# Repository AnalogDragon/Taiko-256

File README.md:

# Taiko-256  
Taiko JVS for Namco System 256 (246)  

Previously, running Taiko on Namco System 256 required many accessories, such as a JVS (MINI-JV PCB), a SIF PCB, and an intermediate FUTA PCB, making the setup overly complex.  
This project's PCB can fully replace the three boards mentioned above. It features two independent Taiko interfaces, an onboard Service button, and supports direct power supply via ATX.  
Alternatively, this PCB can also be used to replace only the SIF PCB and FUTA PCB while still using the original MINI-JV PCB. However, this does not provide a better experience.  

## PCB:  

**Labels in the image:**  
- **A**: Taiko sensor interface. Channels 1\~4 are for Player 1, and channels 5\~8 are for Player 2. Requires connection to a Taiko with vibration sensors (the pins near the board edge are for grounding).  
- **B**: Taiko sensor input swap matrix. Jumpers can be placed in different positions to map inputs to any channel.  
- **C**: Interface for connecting to MINI-JV (can be left unconnected).  
- **D**: When connecting to MINI-JV, determines whether drum signals come from the MCU or SIF (can be left unconnected).  
- **E**: Requires three jumpers to be vertically shorted. If MINI-JV is connected, remove all three jumpers.  
- **F**: Interface for connecting to System 256. Either vertical or right-angle connectors can be soldered (ensure correct placement). For data communication, a USB-A to USB-B cable is required. For System 256 power, a VH3.96-6Pin double-ended reverse cable is needed.  
- **G**: ATX power connector. Either vertical or right-angle connectors can be soldered.  
- **H**: Power switch (requires a latching switch). Press to activate the ATX power supply.  
- **I**: Used for debug.  
- **J**: Configuration code (from left to right, digits 1~4):  
  - **1**: Debug switch (set to OFF during use).  
  - **2**: Frequency limiter switch (set to ON during use, as the System cannot handle overly fast inputs).  
  - **3**: Automatic DON allocation (if the left DON is hit multiple times, System 256 may fail to recognize excessive inputs. Allocating it to the right channel improves the experience. Recommended: ON).  
  - **4**: JVS function (set to ON. Set to OFF if connecting to MINI-JV).  
- **K**: Service function buttons. TEST requires a latching switch, while the others require momentary switches.  
- **L**: Connector for linking to a Service control panel. If the Service buttons need to be extended to another panel, this connector can be used.  

### PCB Image:

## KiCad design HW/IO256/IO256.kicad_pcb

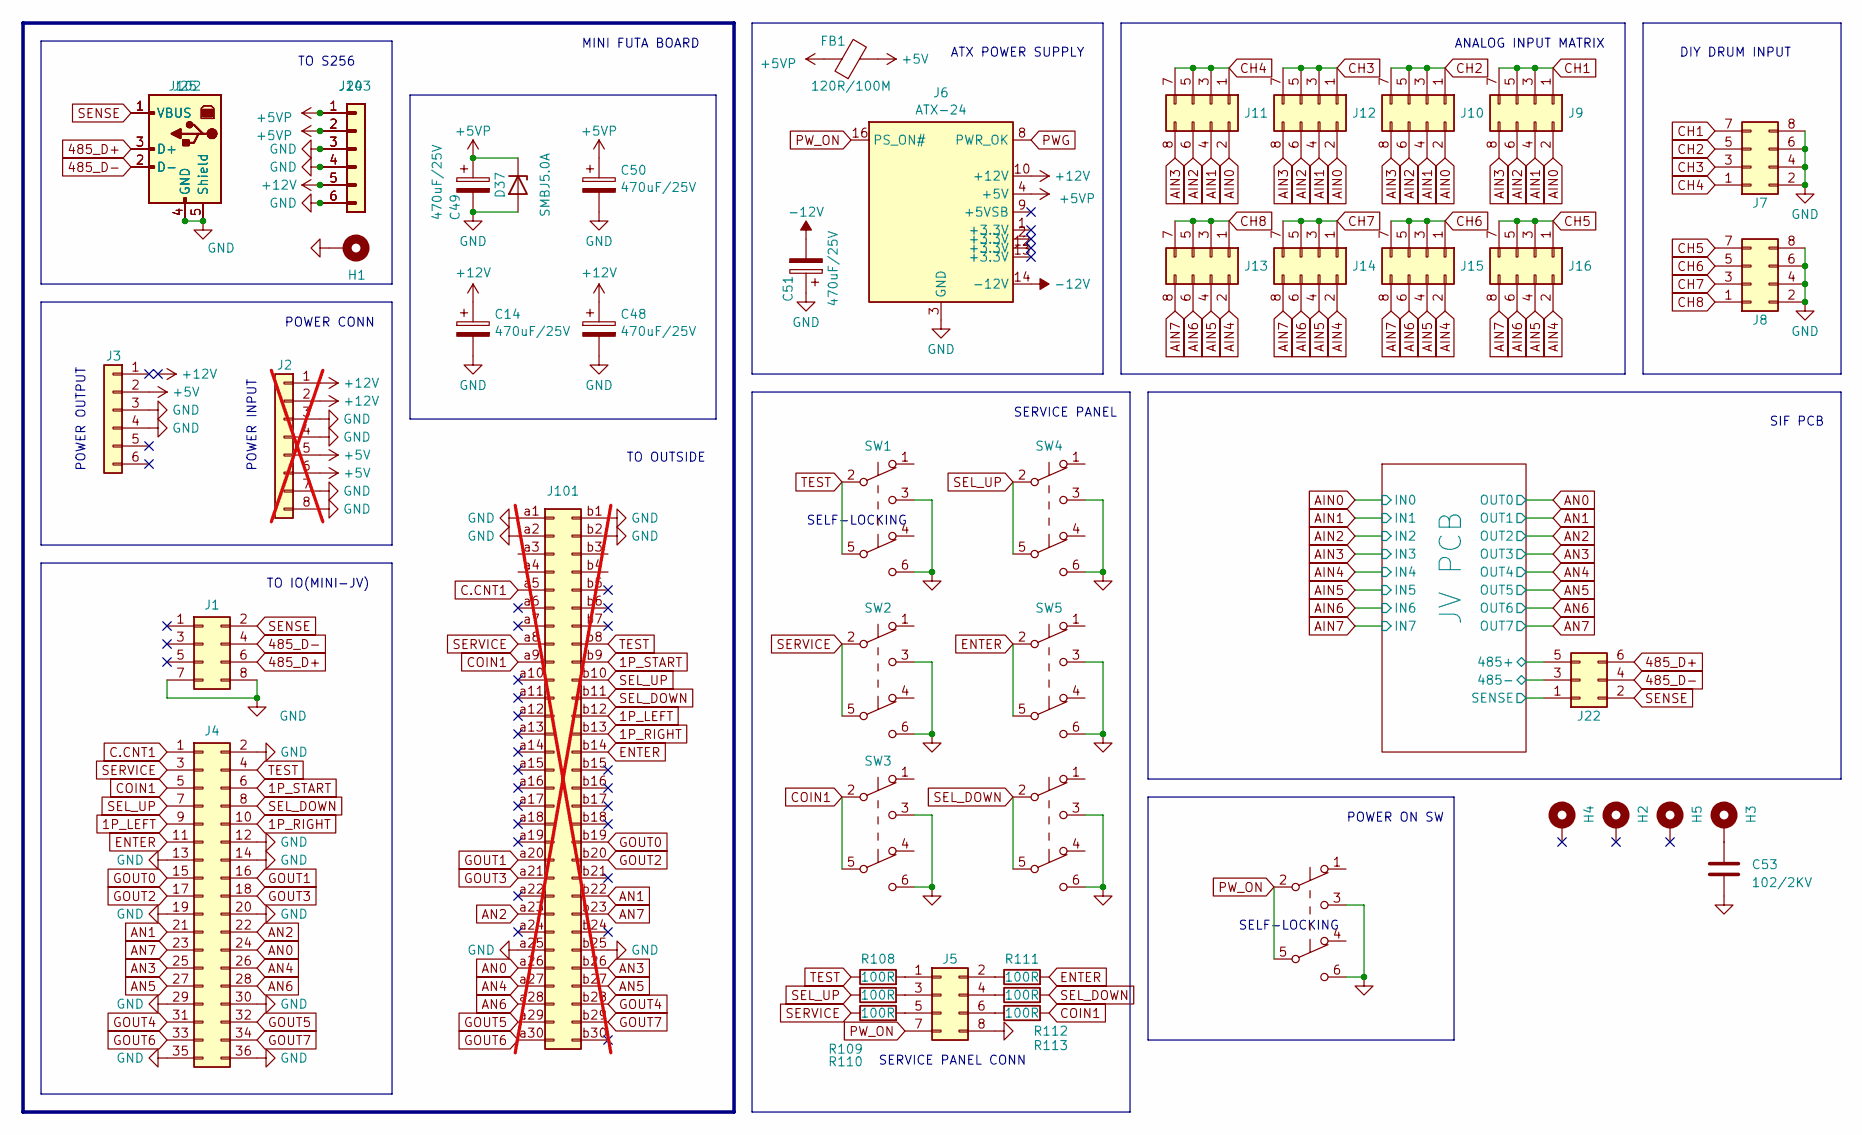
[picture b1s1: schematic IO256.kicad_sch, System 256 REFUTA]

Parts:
C14, C48, C49, C50, C51: 470uF/25V; CP_Radial_D8.0mm_P3.50mm
C53: 102/2KV; C_1206_3216Metric
D37: SMBJ5.0A; D_SMB
FB1: 120R/100M; R_0805_2012Metric
H1, H2, H3, H4, H5: MINI-JV; MountingHole_3.2mm_M3_DIN965_Pad
J1: Conn_02x04_Odd_Even; B08B-XADSS-N-A
J2: Conn_01x08; JST_VH_B8P-VH-B_1x08_P3.96mm_Vertical; not fitted
J3, J103: Conn_01x06; JST_VH_B6P-VH_1x06_P3.96mm_Vertical
J4: Conn_02x18_Odd_Even; B36B-XADSS-N-A
J5, J7, J8: Conn_02x04_Counter_Clockwise; IDC-Header_2x04_P2.54mm_Vertical
J6: ATX-24; 5557-2x12
J9, J10, J11, J12, J13, J14, J15, J16: Conn_02x04_Counter_Clockwise; PinHeader_2x04_P2.54mm_Vertical
J22: Conn_02x02_Odd_Even; PinHeader_2x03_P2.54mm_Vertical
J24: Conn_01x06; JST_VH_B6PS-VH_1x06_P3.96mm_Horizontal
J25: USB_B; USB_B_OST_USB-B1HSxx_Horizontal
J101: Conn_02x30_Row_Letter_First; IDC-Header_2x30_P2.54mm_Latch6.5mm_Vertical; not fitted
J102: USB_B; USB_B_TE_5787834_Vertical
R108, R109, R110, R111, R112, R113: 100R; R_0603_1608Metric
SW1, SW8: SW6*6_selflock; switch_6x6
SW2, SW3, SW4, SW5, SW6: SW6*6_button; switch_6x6

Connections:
1P_LEFT: J4.9, J101.b12
1P_RIGHT: J4.10, J101.b13
1P_START: J4.6, J101.b9
485_D+: J1.6, J22.6, J25.3 (D+), J102.3 (D+)
485_D-: J1.4, J22.4, J25.2 (D-), J102.2 (D-)
+5V: FB1.2, J2.5, J2.6, J3.2; also elsewhere on the board
+5VP: C49.1, C50.1, D37.1 (K), FB1.1, J6.4 (+5V), J6.6 (+5V), J6.21 (+5V), J6.22 (+5V), J6.23 (+5V), J24.1, J24.2, J103.1, J103.2
+12V: C14.1, C48.1, J2.1, J2.2, J6.10 (+12V), J6.11 (+12V), J24.5, J103.5
-12V: C51.2, J6.14 (-12V); also elsewhere on the board
/JV PCB/485+: J22.5; also elsewhere on the board
/JV PCB/485-: J22.3; also elsewhere on the board
/JV PCB/SENSE: J22.1; also elsewhere on the board
AIN0: J9.2, J10.2, J11.2, J12.2; also elsewhere on the board
AIN1: J9.4, J10.4, J11.4, J12.4; also elsewhere on the board
AIN2: J9.6, J10.6, J11.6, J12.6; also elsewhere on the board
AIN3: J9.8, J10.8, J11.8, J12.8; also elsewhere on the board
AIN4: J13.2, J14.2, J15.2, J16.2; also elsewhere on the board
AIN5: J13.4, J14.4, J15.4, J16.4; also elsewhere on the board
AIN6: J13.6, J14.6, J15.6, J16.6; also elsewhere on the board
AIN7: J13.8, J14.8, J15.8, J16.8; also elsewhere on the board
AN0: J4.24, J101.a26; also elsewhere on the board
AN1: J4.21, J101.b22; also elsewhere on the board
AN2: J4.22, J101.a23; also elsewhere on the board
AN3: J4.25, J101.b26; also elsewhere on the board
AN4: J4.26, J101.a27; also elsewhere on the board
AN5: J4.27, J101.b27; also elsewhere on the board
AN6: J4.28, J101.a28; also elsewhere on the board
AN7: J4.23, J101.b23; also elsewhere on the board
C.CNT1: J4.1, J101.a5
CH1: J7.7, J9.1, J9.3, J9.5, J9.7
CH2: J7.5, J10.1, J10.3, J10.5, J10.7
CH3: J7.3, J12.1, J12.3, J12.5, J12.7
CH4: J7.1, J11.1, J11.3, J11.5, J11.7
CH5: J8.7, J16.1, J16.3, J16.5, J16.7
CH6: J8.5, J15.1, J15.3, J15.5, J15.7
CH7: J8.3, J14.1, J14.3, J14.5, J14.7
CH8: J8.1, J13.1, J13.3, J13.5, J13.7
COIN1: J4.5, R113.2, SW3.2 (B), SW3.5 (B); also elsewhere on the board
ENTER: J4.11, R111.2, SW5.2 (B), SW5.5 (B); also elsewhere on the board
GND: C14.2, C48.2, C49.2, C50.2, C51.1, C53.2, D37.2 (A), H1.1, J1.7, J1.8, J2.3, J2.4, J2.7, J2.8, J3.3, J3.4, J4.2, J4.12, J4.13, J4.14, J4.19, J4.20, J4.29, J4.30, J4.35, J4.36, J5.8, J6.3 (GND), J6.5 (GND), J6.7 (GND), J6.15 (GND), J6.17 (GND), J6.18 (GND), J6.19 (GND), J6.24 (GND), J7.2, J7.4, J7.6, J7.8, J8.2, J8.4, J8.6, J8.8, J24.3, J24.4, J24.6, J25.4 (GND), J25.5 (Shield), J101.a1, J101.a2, J101.a25, J101.b1, J101.b2, J101.b25, J102.4 (GND), J102.5 (Shield), J103.3, J103.4, J103.6, SW1.3 (C), SW1.6 (C), SW2.3 (C), SW2.6 (C), SW3.3 (C), SW3.6 (C), SW4.3 (C), SW4.6 (C), SW5.3 (C), SW5.6 (C), SW6.3 (C), SW6.6 (C), SW8.3 (C), SW8.6 (C); also elsewhere on the board
GOUT0: J4.15, J101.b19
GOUT1: J4.16, J101.a20
GOUT2: J4.17, J101.b20
GOUT3: J4.18, J101.a21
GOUT4: J4.31, J101.b28
GOUT5: J4.32, J101.a29
GOUT6: J4.33, J101.a30
GOUT7: J4.34, J101.b29
unnamed: C53.1, H3.1
unnamed: J5.1, R108.2
unnamed: J5.2, R111.1
unnamed: J5.3, R109.2
unnamed: J5.4, R112.1
unnamed: J5.5, R110.2
unnamed: J5.6, R113.1
PWG: J6.8 (PWR_OK)
PW_ON: J5.7, J6.16 (PS_ON#), SW8.2 (B), SW8.5 (B)
SEL_DOWN: J4.8, R112.2, SW6.2 (B), SW6.5 (B); also elsewhere on the board
SEL_UP: J4.7, R109.1, SW4.2 (B), SW4.5 (B); also elsewhere on the board
SENSE: J1.2, J22.2, J25.1 (VBUS), J102.1 (VBUS)
SERVICE: J4.3, R110.1, SW2.2 (B), SW2.5 (B); also elsewhere on the board
TEST: J4.4, R108.1, SW1.2 (B), SW1.5 (B); also elsewhere on the board

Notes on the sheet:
SERVICE PANEL CONN
DIY DRUM INPUT
SERVICE PANEL
ANALOG INPUT MATRIX
SELF-LOCKING
TO S256
SIF PCB
MINI FUTA BOARD
POWER OUTPUT
TO OUTSIDE
TO IO(MINI-JV)
POWER CONN
ATX POWER SUPPLY
POWER INPUT
POWER ON SW

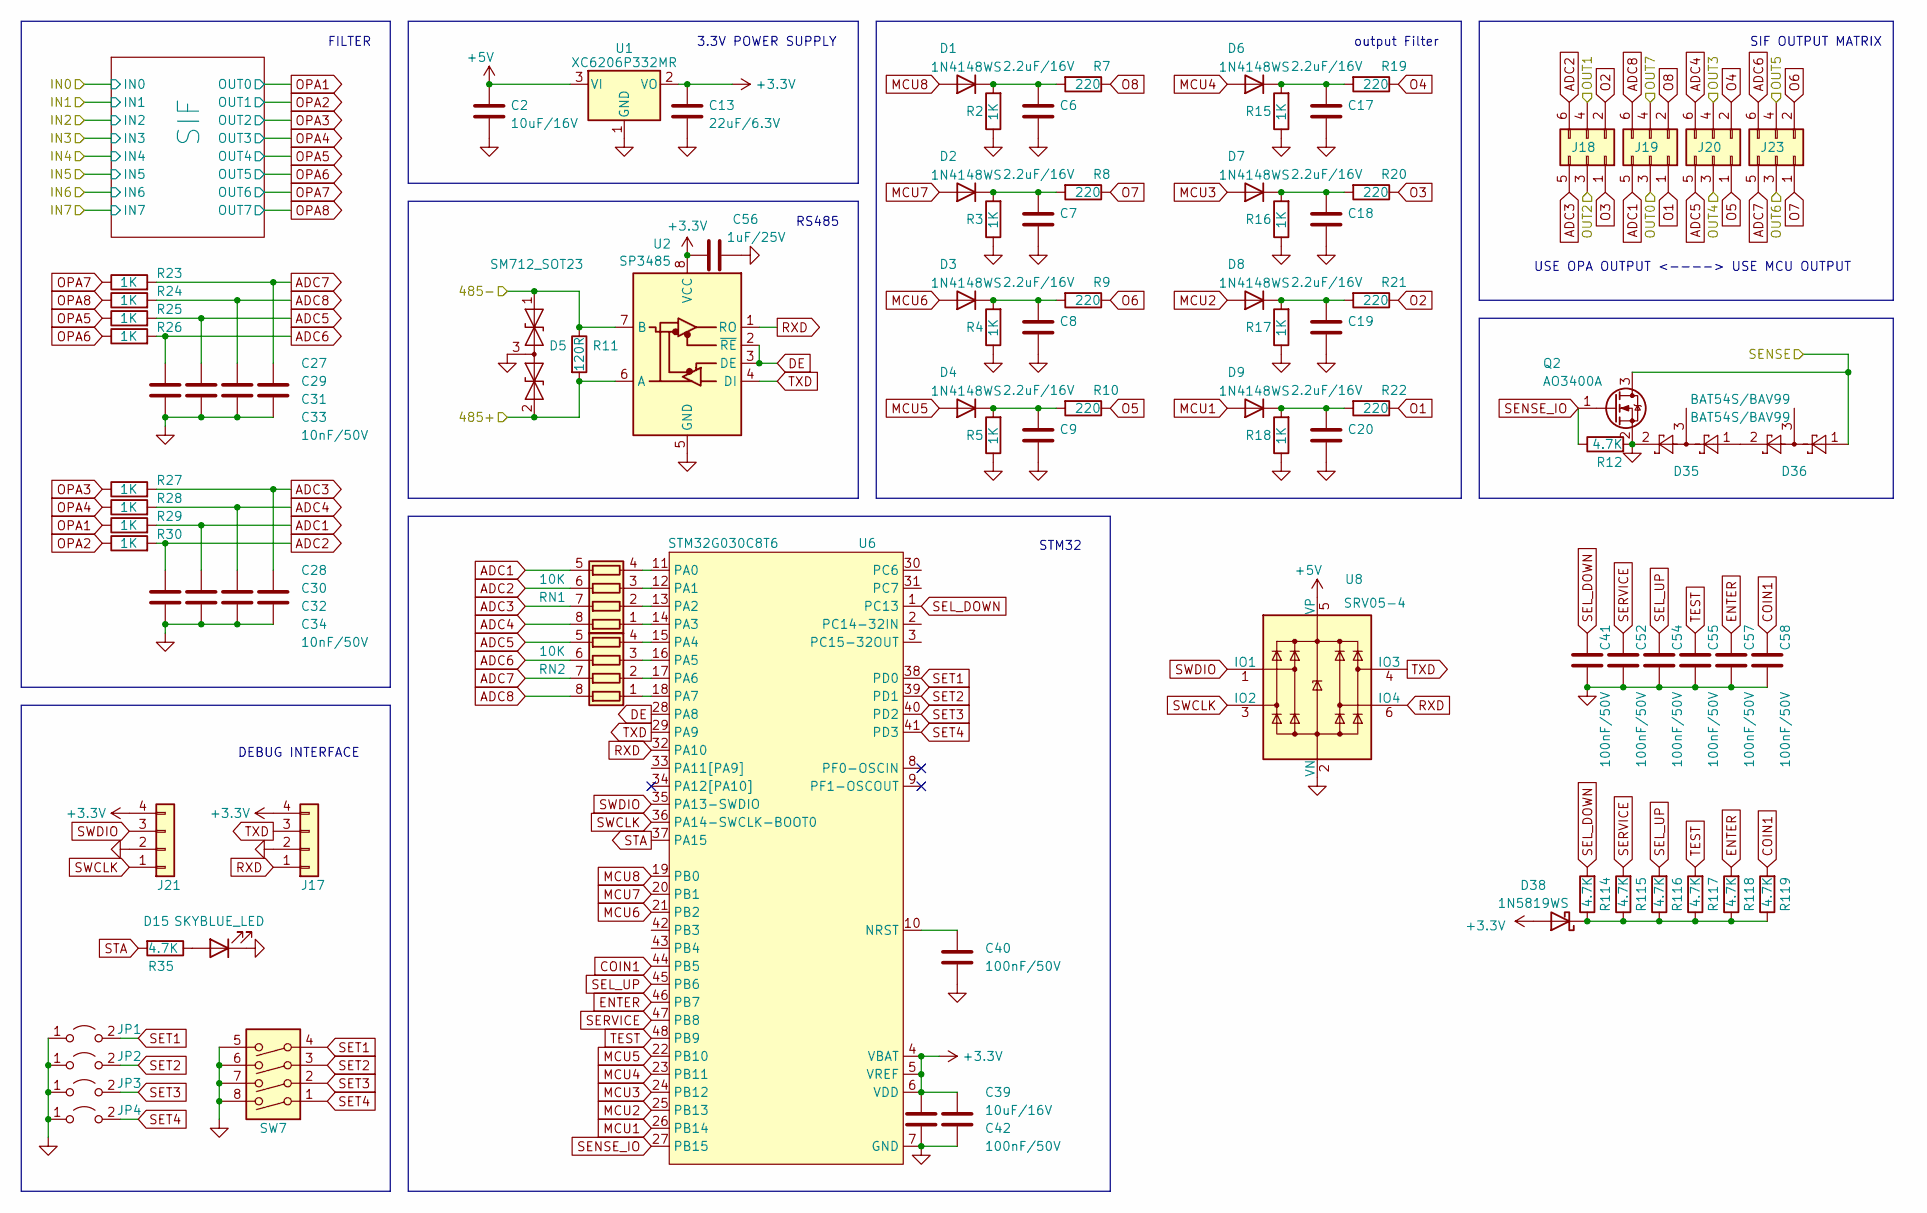
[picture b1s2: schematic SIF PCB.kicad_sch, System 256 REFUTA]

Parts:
C2, C39: 10uF/16V; C_0603_1608Metric
C6, C7, C8, C9, C17, C18, C19, C20: 2.2uF/16V; C_0603_1608Metric
C13: 22uF/6.3V; C_0603_1608Metric
C27, C28, C29, C30, C31, C32, C33, C34: 10nF/50V; C_0603_1608Metric
C40, C42: 100nF/50V; C_0603_1608Metric
C41, C52, C54, C55, C57, C58: 100nF/50V; C_0402_1005Metric
C56: 1uF/25V; C_0603_1608Metric
D1, D2, D3, D4, D6, D7, D8, D9: 1N4148WS; D_SOD-323_HandSoldering
D5: SM712_SOT23; SOT-23
D15: SKYBLUE_LED; LED_0603_1608Metric
D35, D36: BAT54S/BAV99; SOT-23
D38: 1N5819WS; D_SOD-323_HandSoldering
J17, J21: Conn_01x04; PinHeader_1x04_P2.54mm_Horizontal
J18, J19, J20, J23: Conn_02x03_Odd_Even; PinHeader_2x03_P2.54mm_Vertical
JP1, JP2, JP3, JP4: Jumper_2_Open; JP_0603
Q2: AO3400A; SOT-23
R2, R3, R4, R5, R15, R16, R17, R18, R23, R24, R25, R26, R27, R28, R29, R30: 1K; R_0603_1608Metric
R7, R8, R9, R10, R19, R20, R21, R22: 220; R_0603_1608Metric
R11: 120R; R_0805_2012Metric
R12, R35: 4.7K; R_0603_1608Metric
R114, R115, R116, R117, R118, R119: 4.7K; R_0402_1005Metric
RN1, RN2: 10K; R_Array_Convex_4x0603
SW7: SW_DIP_x04; SW_DIP_SPSTx04_Slide_9.78x12.34mm_W7.62mm_P2.54mm
U1: XC6206P332MR; SOT-23
U2: SP3485; SOIC-8_3.9x4.9mm_P1.27mm
U6: STM32G030C8T6; LQFP-48_7x7mm_P0.5mm
U8: SRV05-4; SOT-23-6

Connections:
+3.3V: C13.1, C39.1, C42.1, C56.1, D38.2 (A), J17.4, J21.4, U1.2 (VO), U2.8 (VCC), U6.4 (VBAT), U6.5 (VREF), U6.6 (VDD)
+5V: C2.1, U1.3 (VI), U8.5 (VP); also elsewhere on the board
/JV PCB/485+: D5.2 (A2), R11.2, U2.6 (A); also elsewhere on the board
/JV PCB/485-: D5.1 (A1), R11.1, U2.7 (B); also elsewhere on the board
/JV PCB/SENSE: D36.1, Q2.3 (D); also elsewhere on the board
ADC1: C30.1, J19.5, R29.2, RN1.5 (R4.2)
ADC2: C28.1, J18.6, R30.2, RN1.6 (R3.2)
ADC3: C34.1, J18.5, R27.2, RN1.7 (R2.2)
ADC4: C32.1, J20.6, R28.2, RN1.8 (R1.2)
ADC5: C29.1, J20.5, R25.2, RN2.5 (R4.2)
ADC6: C27.1, J23.6, R26.2, RN2.6 (R3.2)
ADC7: C33.1, J23.5, R23.2, RN2.7 (R2.2)
ADC8: C31.1, J19.6, R24.2, RN2.8 (R1.2)
AN0: J19.3; also elsewhere on the board
AN1: J18.4; also elsewhere on the board
AN2: J18.3; also elsewhere on the board
AN3: J20.4; also elsewhere on the board
AN4: J20.3; also elsewhere on the board
AN5: J23.4; also elsewhere on the board
AN6: J23.3; also elsewhere on the board
AN7: J19.4; also elsewhere on the board
COIN1: C58.1, R119.2, U6.44 (PB5); also elsewhere on the board
DE: U2.2 (~RE), U2.3 (DE), U6.28 (PA8)
ENTER: C57.1, R118.2, U6.46 (PB7); also elsewhere on the board
GND: C2.2, C6.1, C7.1, C8.1, C9.1, C13.2, C17.1, C18.1, C19.1, C20.1, C27.2, C28.2, C29.2, C30.2, C31.2, C32.2, C33.2, C34.2, C39.2, C40.2, C41.2, C42.2, C52.2, C54.2, C55.2, C56.2, C57.2, C58.2, D5.3 (common), D15.1 (K), D35.2, J17.2, J21.2, JP1.1 (A), JP2.1 (A), JP3.1 (A), JP4.1 (A), Q2.2 (S), R2.1, R3.1, R4.1, R5.1, R12.2, R15.1, R16.1, R17.1, R18.1, SW7.5, SW7.6, SW7.7, SW7.8, U1.1 (GND), U2.5 (GND), U6.7 (GND), U8.2 (VN); also elsewhere on the board
MCU1: D9.2 (A), U6.26 (PB14)
MCU2: D8.2 (A), U6.25 (PB13)
MCU3: D7.2 (A), U6.24 (PB12)
MCU4: D6.2 (A), U6.23 (PB11)
MCU5: D4.2 (A), U6.22 (PB10)
MCU6: D3.2 (A), U6.21 (PB2)
MCU7: D2.2 (A), U6.20 (PB1)
MCU8: D1.2 (A), U6.19 (PB0)
unnamed: C6.2, D1.1 (K), R2.2, R7.2
unnamed: C7.2, D2.1 (K), R3.2, R8.2
unnamed: C8.2, D3.1 (K), R4.2, R9.2
unnamed: C9.2, D4.1 (K), R5.2, R10.2
unnamed: C17.2, D6.1 (K), R15.2, R19.2
unnamed: C18.2, D7.1 (K), R16.2, R20.2
unnamed: C19.2, D8.1 (K), R17.2, R21.2
unnamed: C20.2, D9.1 (K), R18.2, R22.2
unnamed: D15.2 (A), R35.1
unnamed: D35.1, D36.2
unnamed: D38.1 (K), R114.1, R115.1, R116.1, R117.1, R118.1, R119.1
unnamed: RN1.1 (R1.1), U6.14 (PA3)
unnamed: RN1.2 (R2.1), U6.13 (PA2)
unnamed: RN1.3 (R3.1), U6.12 (PA1)
unnamed: RN1.4 (R4.1), U6.11 (PA0)
unnamed: RN2.1 (R1.1), U6.18 (PA7)
unnamed: RN2.2 (R2.1), U6.17 (PA6)
unnamed: RN2.3 (R3.1), U6.16 (PA5)
unnamed: RN2.4 (R4.1), U6.15 (PA4)
unnamed: C40.1, U6.10 (NRST)
O1: J19.1, R22.1
O2: J18.2, R21.1
O3: J18.1, R20.1
O4: J20.2, R19.1
O5: J20.1, R10.1
O6: J23.2, R9.1
O7: J23.1, R8.1
O8: J19.2, R7.1
OPA1: R29.1; also elsewhere on the board
OPA2: R30.1; also elsewhere on the board
OPA3: R27.1; also elsewhere on the board
OPA4: R28.1; also elsewhere on the board
OPA5: R25.1; also elsewhere on the board
OPA6: R26.1; also elsewhere on the board
OPA7: R23.1; also elsewhere on the board
OPA8: R24.1; also elsewhere on the board
RXD: J17.1, U2.1 (RO), U6.32 (PA10), U8.6 (IO4)
SEL_DOWN: C41.1, R114.2, U6.1 (PC13); also elsewhere on the board
SEL_UP: C54.1, R116.2, U6.45 (PB6); also elsewhere on the board
SENSE_IO: Q2.1 (G), R12.1, U6.27 (PB15)
SERVICE: C52.1, R115.2, U6.47 (PB8); also elsewhere on the board
SET1: JP1.2 (B), SW7.4, U6.38 (PD0)
SET2: JP2.2 (B), SW7.3, U6.39 (PD1)
SET3: JP3.2 (B), SW7.2, U6.40 (PD2)
SET4: JP4.2 (B), SW7.1, U6.41 (PD3)
STA: R35.2, U6.37 (PA15)
SWCLK: J21.1, U6.36 (PA14-SWCLK-BOOT0), U8.3 (IO2)
SWDIO: J21.3, U6.35 (PA13-SWDIO), U8.1 (IO1)
TEST: C55.1, R117.2, U6.48 (PB9); also elsewhere on the board
TXD: J17.3, U2.4 (DI), U6.29 (PA9), U8.4 (IO3)

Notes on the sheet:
SIF OUTPUT MATRIX
DEBUG INTERFACE
STM32
3.3V POWER SUPPLY
RS485
output Filter
USE OPA OUTPUT <----> USE MCU OUTPUT
FILTER

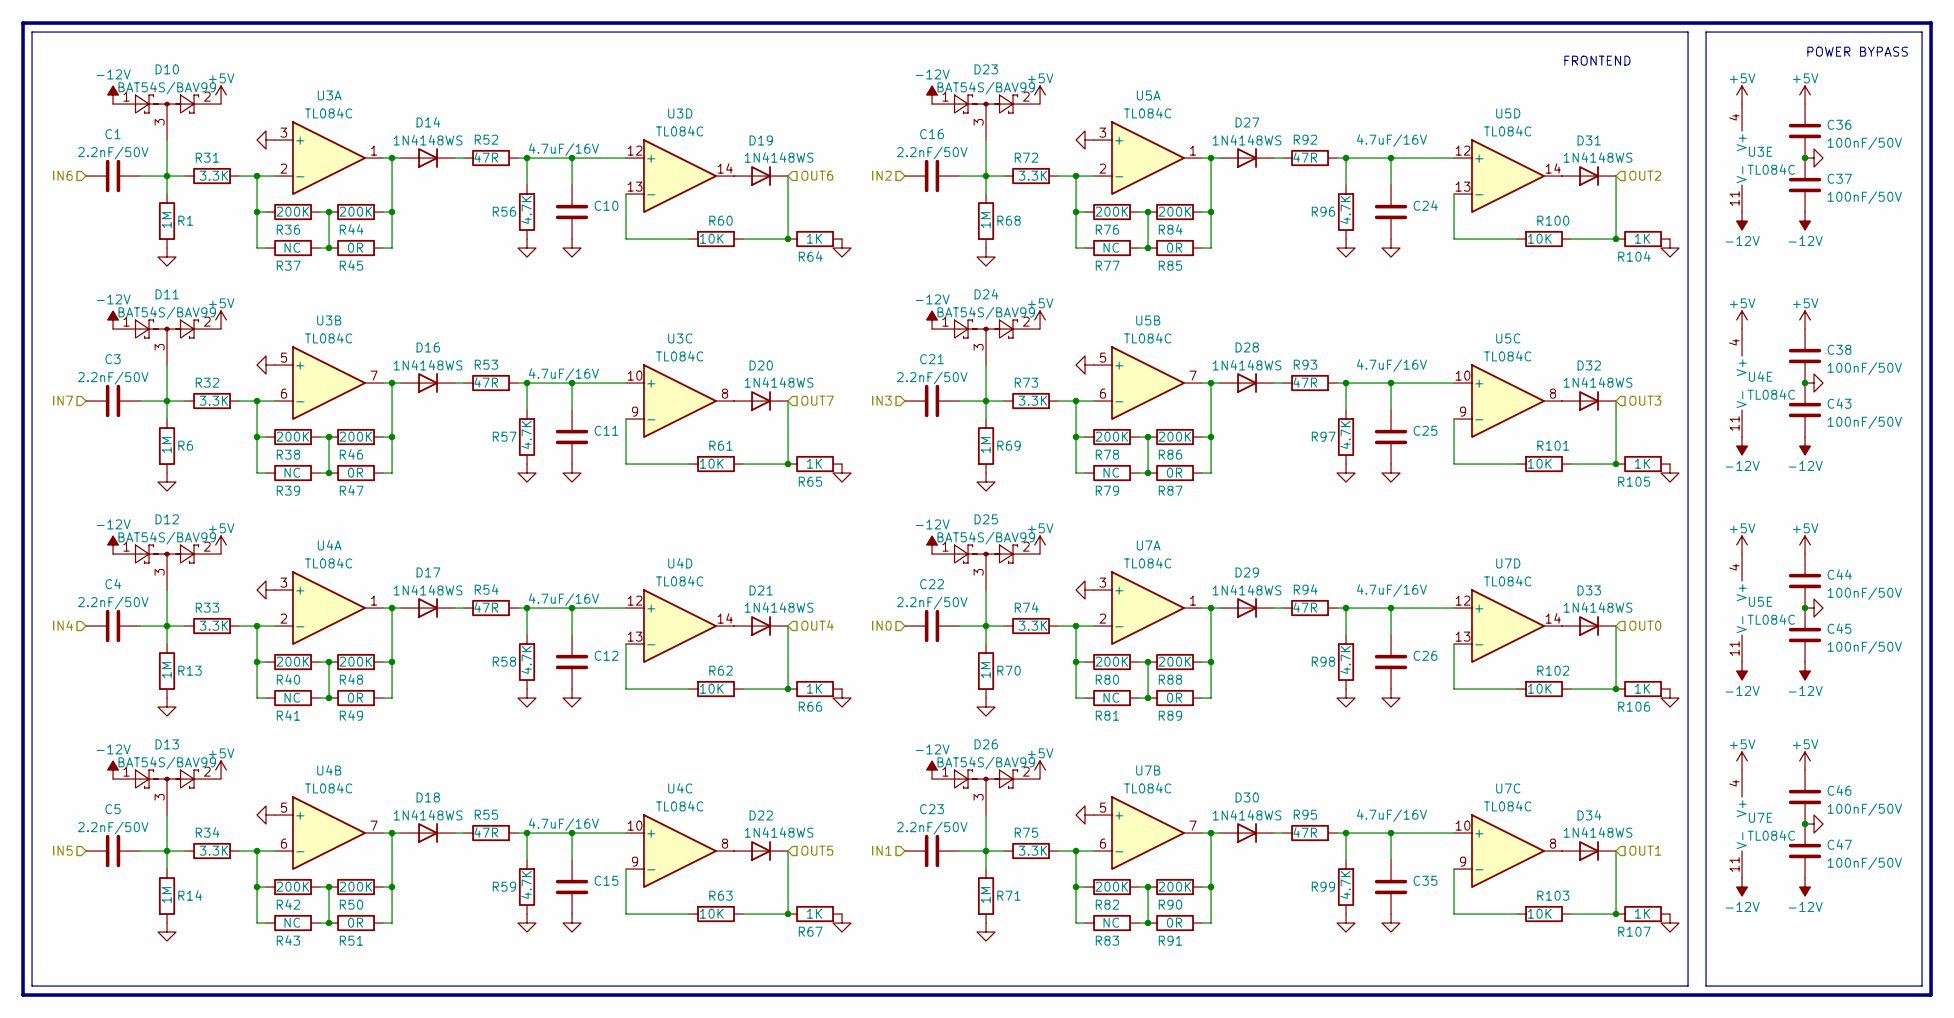
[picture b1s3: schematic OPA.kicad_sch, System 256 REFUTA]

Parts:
C1, C3, C4, C5, C16, C21, C22, C23: 2.2nF/50V; C_0603_1608Metric
C10, C11, C12, C15, C24, C25, C26, C35: 4.7uF/16V; C_0603_1608Metric
C36, C37, C38, C43, C44, C45, C46, C47: 100nF/50V; C_0603_1608Metric
D10, D11, D12, D13, D23, D24, D25, D26: BAT54S/BAV99; SOT-23
D14, D16, D17, D18, D19, D20, D21, D22, D27, D28, D29, D30, D31, D32, D33, D34: 1N4148WS; D_SOD-323_HandSoldering
R1, R6, R13, R14, R68, R69, R70, R71: 1M; R_0603_1608Metric
R31, R32, R33, R34, R72, R73, R74, R75: 3.3K; R_0603_1608Metric
R36, R38, R40, R42, R44, R46, R48, R50, R76, R78, R80, R82, R84, R86, R88, R90: 200K; R_0603_1608Metric
R37, R39, R41, R43, R77, R79, R81, R83: NC; R_0603_1608Metric
R45, R47, R49, R51, R85, R87, R89, R91: 0R; R_0603_1608Metric
R52, R53, R54, R55, R92, R93, R94, R95: 47R; R_0603_1608Metric
R56, R57, R58, R59, R96, R97, R98, R99: 4.7K; R_0603_1608Metric
R60, R61, R62, R63, R100, R101, R102, R103: 10K; R_0603_1608Metric
R64, R65, R66, R67, R104, R105, R106, R107: 1K; R_0603_1608Metric
U3, U4, U5, U7: TL084C; SO-14_3.9x8.65mm_P1.27mm

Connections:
+5V: C36.2, C38.2, C44.2, C46.2, D10.2, D11.2, D12.2, D13.2, D23.2, D24.2, D25.2, D26.2, U3.4 (V+), U4.4 (V+), U5.4 (V+), U7.4 (V+); also elsewhere on the board
-12V: C37.1, C43.1, C45.1, C47.1, D10.1, D11.1, D12.1, D13.1, D23.1, D24.1, D25.1, D26.1, U3.11 (V-), U4.11 (V-), U5.11 (V-), U7.11 (V-); also elsewhere on the board
AIN0: C22.1; also elsewhere on the board
AIN1: C23.1; also elsewhere on the board
AIN2: C16.1; also elsewhere on the board
AIN3: C21.1; also elsewhere on the board
AIN4: C4.1; also elsewhere on the board
AIN5: C5.1; also elsewhere on the board
AIN6: C1.1; also elsewhere on the board
AIN7: C3.1; also elsewhere on the board
GND: C10.1, C11.1, C12.1, C15.1, C24.1, C25.1, C26.1, C35.1, C36.1, C37.2, C38.1, C43.2, C44.1, C45.2, C46.1, C47.2, R1.2, R6.2, R13.2, R14.2, R56.1, R57.1, R58.1, R59.1, R64.2, R65.2, R66.2, R67.2, R68.2, R69.2, R70.2, R71.2, R96.1, R97.1, R98.1, R99.1, R104.2, R105.2, R106.2, R107.2, U3.3 (+), U3.5 (+), U4.3 (+), U4.5 (+), U5.3 (+), U5.5 (+), U7.3 (+), U7.5 (+); also elsewhere on the board
unnamed: C1.2, D10.3, R1.1, R31.1
unnamed: C3.2, D11.3, R6.1, R32.1
unnamed: C4.2, D12.3, R13.1, R33.1
unnamed: C5.2, D13.3, R14.1, R34.1
unnamed: C16.2, D23.3, R68.1, R72.1
unnamed: C21.2, D24.3, R69.1, R73.1
unnamed: C22.2, D25.3, R70.1, R74.1
unnamed: C23.2, D26.3, R71.1, R75.1
unnamed: D14.2 (A), R44.2, R45.2, U3.1
unnamed: D14.1 (K), R52.1
unnamed: D16.2 (A), R46.2, R47.2, U3.7
unnamed: D16.1 (K), R53.1
unnamed: D17.2 (A), R48.2, R49.2, U4.1
unnamed: D17.1 (K), R54.1
unnamed: D18.2 (A), R50.2, R51.2, U4.7
unnamed: D18.1 (K), R55.1
unnamed: D19.2 (A), U3.14
unnamed: D20.2 (A), U3.8
unnamed: D21.2 (A), U4.14
unnamed: D22.2 (A), U4.8
unnamed: D27.2 (A), R84.2, R85.2, U5.1
unnamed: D27.1 (K), R92.1
unnamed: D28.2 (A), R86.2, R87.2, U5.7
unnamed: D28.1 (K), R93.1
unnamed: D29.2 (A), R88.2, R89.2, U7.1
unnamed: D29.1 (K), R94.1
unnamed: D30.2 (A), R90.2, R91.2, U7.7
unnamed: D30.1 (K), R95.1
unnamed: D31.2 (A), U5.14
unnamed: D32.2 (A), U5.8
unnamed: D33.2 (A), U7.14
unnamed: D34.2 (A), U7.8
unnamed: R36.2, R37.2, R44.1, R45.1
unnamed: R38.2, R39.2, R46.1, R47.1
unnamed: R40.2, R41.2, R48.1, R49.1
unnamed: R42.2, R43.2, R50.1, R51.1
unnamed: R76.2, R77.2, R84.1, R85.1
unnamed: R78.2, R79.2, R86.1, R87.1
unnamed: R80.2, R81.2, R88.1, R89.1
unnamed: R82.2, R83.2, R90.1, R91.1
unnamed: R31.2, R36.1, R37.1, U3.2 (-)
unnamed: R32.2, R38.1, R39.1, U3.6 (-)
unnamed: C11.2, R53.2, R57.2, U3.10 (+)
unnamed: R61.2, U3.9 (-)
unnamed: C10.2, R52.2, R56.2, U3.12 (+)
unnamed: R60.2, U3.13 (-)
unnamed: R33.2, R40.1, R41.1, U4.2 (-)
unnamed: R34.2, R42.1, R43.1, U4.6 (-)
unnamed: C15.2, R55.2, R59.2, U4.10 (+)
unnamed: R63.2, U4.9 (-)
unnamed: C12.2, R54.2, R58.2, U4.12 (+)
unnamed: R62.2, U4.13 (-)
unnamed: R72.2, R76.1, R77.1, U5.2 (-)
unnamed: R73.2, R78.1, R79.1, U5.6 (-)
unnamed: C25.2, R93.2, R97.2, U5.10 (+)
unnamed: R101.2, U5.9 (-)
unnamed: C24.2, R92.2, R96.2, U5.12 (+)
unnamed: R100.2, U5.13 (-)
unnamed: R74.2, R80.1, R81.1, U7.2 (-)
unnamed: R75.2, R82.1, R83.1, U7.6 (-)
unnamed: C35.2, R95.2, R99.2, U7.10 (+)
unnamed: R103.2, U7.9 (-)
unnamed: C26.2, R94.2, R98.2, U7.12 (+)
unnamed: R102.2, U7.13 (-)
OPA1: D33.1 (K), R102.1, R106.1; also elsewhere on the board
OPA2: D34.1 (K), R103.1, R107.1; also elsewhere on the board
OPA3: D31.1 (K), R100.1, R104.1; also elsewhere on the board
OPA4: D32.1 (K), R101.1, R105.1; also elsewhere on the board
OPA5: D21.1 (K), R62.1, R66.1; also elsewhere on the board
OPA6: D22.1 (K), R63.1, R67.1; also elsewhere on the board
OPA7: D19.1 (K), R60.1, R64.1; also elsewhere on the board
OPA8: D20.1 (K), R61.1, R65.1; also elsewhere on the board

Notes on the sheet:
POWER BYPASS
FRONTEND

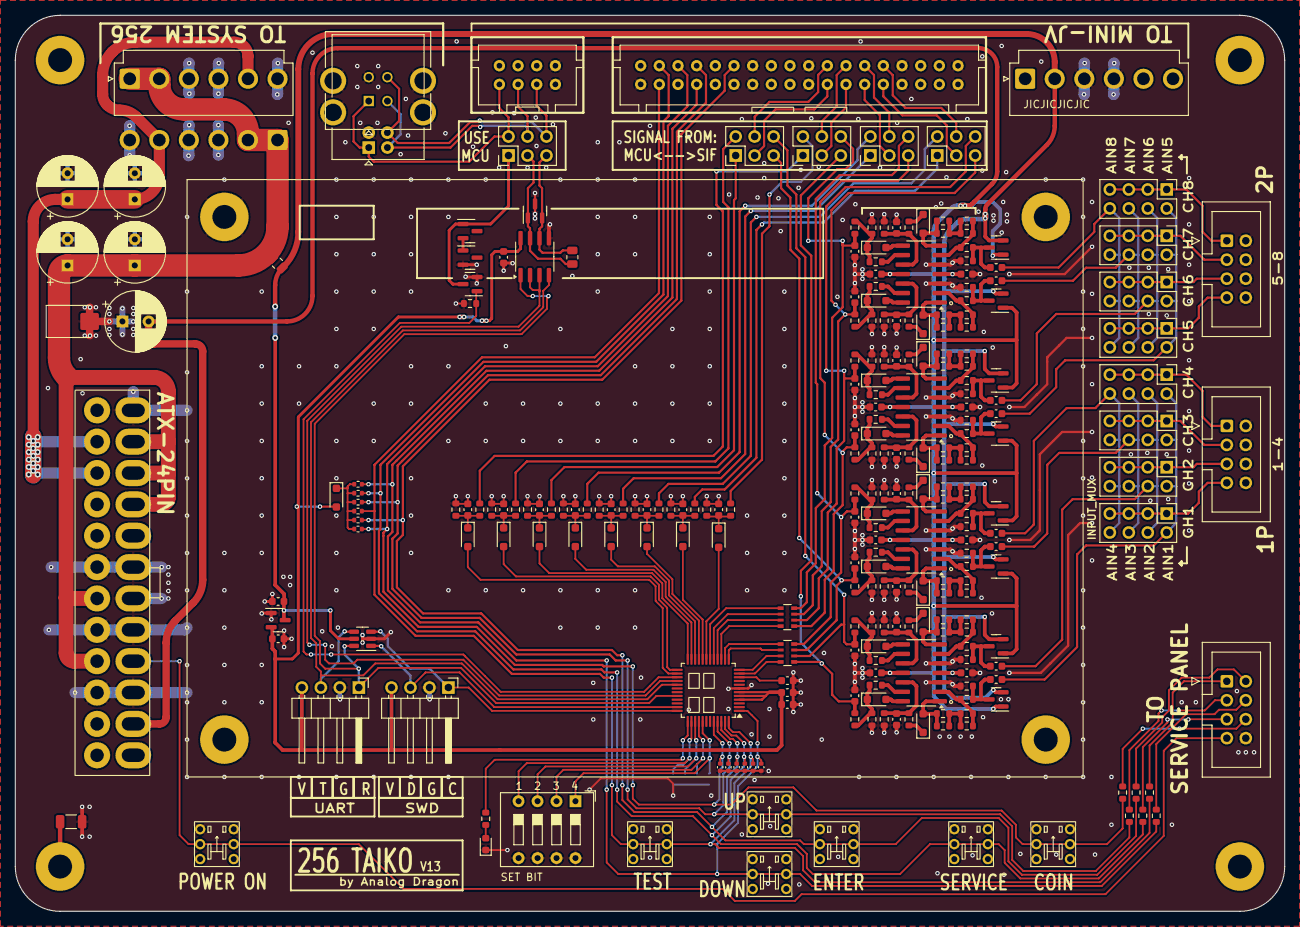
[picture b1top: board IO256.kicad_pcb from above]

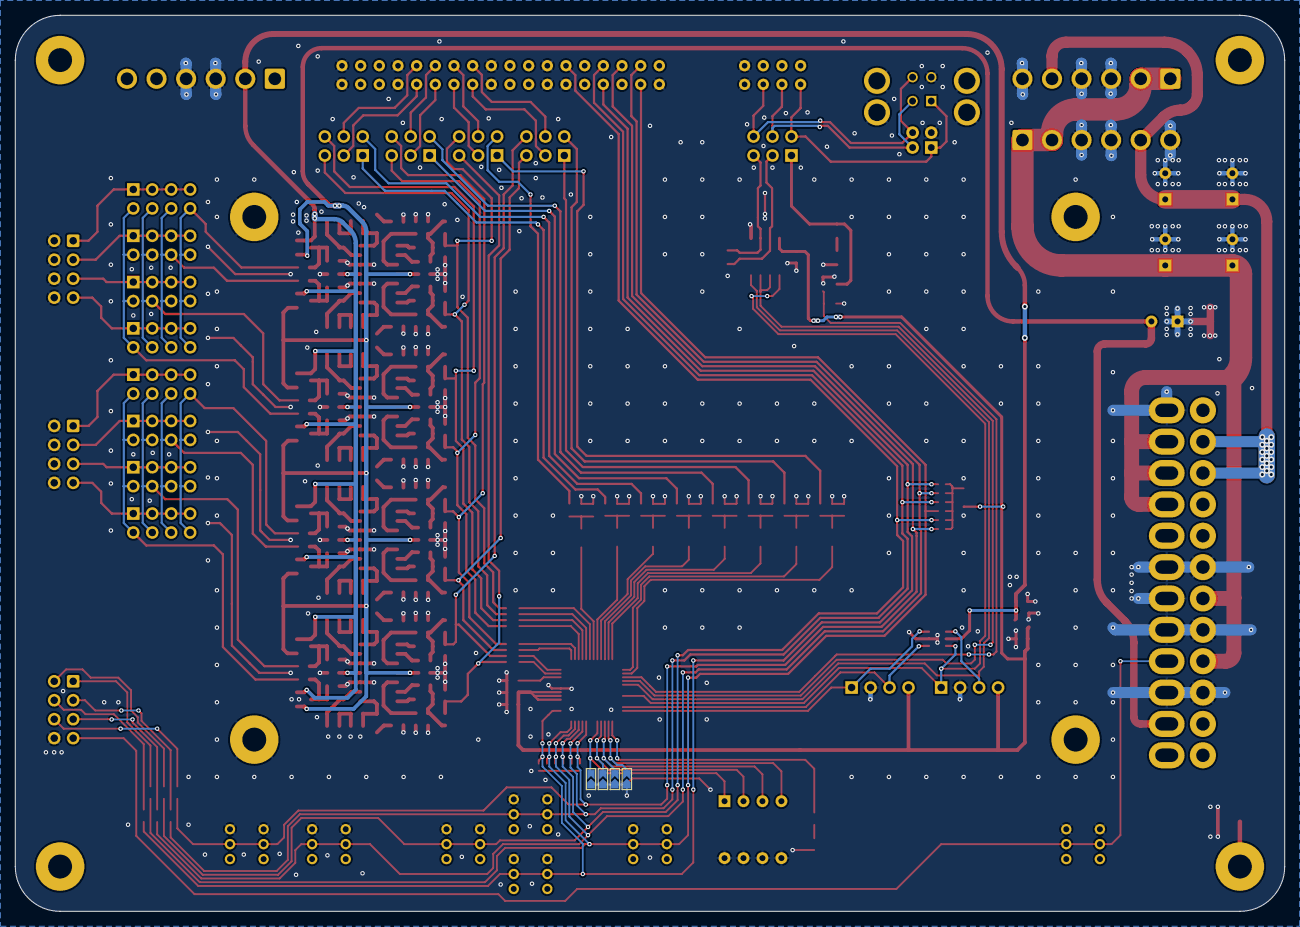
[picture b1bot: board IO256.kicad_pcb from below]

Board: 2 copper layers, 170.0 x 120.0 mm, 270 parts (4 on the bottom side), 177 nets.

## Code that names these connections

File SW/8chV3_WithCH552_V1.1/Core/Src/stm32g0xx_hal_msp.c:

/* USER CODE BEGIN Header */
/**
  ******************************************************************************
  * @file         stm32g0xx_hal_msp.c
  * @brief        This file provides code for the MSP Initialization
  *               and de-Initialization codes.
  ******************************************************************************
  * @attention
  *
  * <h2><center>&copy; Copyright (c) 2021 STMicroelectronics.
  * All rights reserved.</center></h2>
  *
  * This software component is licensed by ST under BSD 3-Clause license,
  * the "License"; You may not use this file except in compliance with the
  * License. You may obtain a copy of the License at:
  *                        opensource.org/licenses/BSD-3-Clause
  *
  ******************************************************************************
  */
/* USER CODE END Header */

/* Includes ------------------------------------------------------------------*/
#include "main.h"
/* USER CODE BEGIN Includes */

/* USER CODE END Includes */
extern DMA_HandleTypeDef hdma_adc1;

extern DMA_HandleTypeDef hdma_usart1_tx;

/* Private typedef -----------------------------------------------------------*/
/* USER CODE BEGIN TD */

/* USER CODE END TD */

/* Private define ------------------------------------------------------------*/
/* USER CODE BEGIN Define */

/* USER CODE END Define */

/* Private macro -------------------------------------------------------------*/
/* USER CODE BEGIN Macro */

/* USER CODE END Macro */

/* Private variables ---------------------------------------------------------*/
/* USER CODE BEGIN PV */

/* USER CODE END PV */

/* Private function prototypes -----------------------------------------------*/
/* USER CODE BEGIN PFP */

/* USER CODE END PFP */

/* External functions --------------------------------------------------------*/
/* USER CODE BEGIN ExternalFunctions */

/* USER CODE END ExternalFunctions */

/* USER CODE BEGIN 0 */

/* USER CODE END 0 */
/**
  * Initializes the Global MSP.
  */
void HAL_MspInit(void)
{
  /* USER CODE BEGIN MspInit 0 */

  /* USER CODE END MspInit 0 */

  __HAL_RCC_SYSCFG_CLK_ENABLE();
  __HAL_RCC_PWR_CLK_ENABLE();

  /* System interrupt init*/

  /* USER CODE BEGIN MspInit 1 */

  /* USER CODE END MspInit 1 */
}

/**
* @brief ADC MSP Initialization
* This function configures the hardware resources used in this example
* @param hadc: ADC handle pointer
* @retval None
*/
void HAL_ADC_MspInit(ADC_HandleTypeDef* hadc)
{
  GPIO_InitTypeDef GPIO_InitStruct = {0};
  if(hadc->Instance==ADC1)
  {
  /* USER CODE BEGIN ADC1_MspInit 0 */

  /* USER CODE END ADC1_MspInit 0 */
    /* Peripheral clock enable */
    __HAL_RCC_ADC_CLK_ENABLE();

    __HAL_RCC_GPIOA_CLK_ENABLE();
    /**ADC1 GPIO Configuration
    PA0     ------> ADC1_IN0
    PA1     ------> ADC1_IN1
    PA2     ------> ADC1_IN2
    PA3     ------> ADC1_IN3
    PA4     ------> ADC1_IN4
    PA5     ------> ADC1_IN5
    PA6     ------> ADC1_IN6
    PA7     ------> ADC1_IN7
    */
    GPIO_InitStruct.Pin = IN1_Pin|IN2_Pin|IN3_Pin|IN4_Pin
                          |IN5_Pin|IN6_Pin|IN7_Pin|IN8_Pin;
    GPIO_InitStruct.Mode = GPIO_MODE_ANALOG;
    GPIO_InitStruct.Pull = GPIO_NOPULL;
    HAL_GPIO_Init(GPIOA, &GPIO_InitStruct);

    /* ADC1 DMA Init */
    /* ADC1 Init */
    hdma_adc1.Instance = DMA1_Channel2;
    hdma_adc1.Init.Request = DMA_REQUEST_ADC1;
    hdma_adc1.Init.Direction = DMA_PERIPH_TO_MEMORY;
    hdma_adc1.Init.PeriphInc = DMA_PINC_DISABLE;
    hdma_adc1.Init.MemInc = DMA_MINC_ENABLE;
    hdma_adc1.Init.PeriphDataAlignment = DMA_PDATAALIGN_HALFWORD;
    hdma_adc1.Init.MemDataAlignment = DMA_MDATAALIGN_HALFWORD;
    hdma_adc1.Init.Mode = DMA_CIRCULAR;
    hdma_adc1.Init.Priority = DMA_PRIORITY_VERY_HIGH;
    if (HAL_DMA_Init(&hdma_adc1) != HAL_OK)
    {
      Error_Handler();
    }

    __HAL_LINKDMA(hadc,DMA_Handle,hdma_adc1);

  /* USER CODE BEGIN ADC1_MspInit 1 */

  /* USER CODE END ADC1_MspInit 1 */
  }

}

/**
* @brief ADC MSP De-Initialization
* This function freeze the hardware resources used in this example
* @param hadc: ADC handle pointer
* @retval None
*/
void HAL_ADC_MspDeInit(ADC_HandleTypeDef* hadc)
{
  if(hadc->Instance==ADC1)
  {
  /* USER CODE BEGIN ADC1_MspDeInit 0 */

  /* USER CODE END ADC1_MspDeInit 0 */
    /* Peripheral clock disable */
    __HAL_RCC_ADC_CLK_DISABLE();

    /**ADC1 GPIO Configuration
    PA0     ------> ADC1_IN0
    PA1     ------> ADC1_IN1
    PA2     ------> ADC1_IN2
    PA3     ------> ADC1_IN3
    PA4     ------> ADC1_IN4
    PA5     ------> ADC1_IN5
    PA6     ------> ADC1_IN6
    PA7     ------> ADC1_IN7
    */
    HAL_GPIO_DeInit(GPIOA, IN1_Pin|IN2_Pin|IN3_Pin|IN4_Pin
                          |IN5_Pin|IN6_Pin|IN7_Pin|IN8_Pin);

    /* ADC1 DMA DeInit */
    HAL_DMA_DeInit(hadc->DMA_Handle);
  /* USER CODE BEGIN ADC1_MspDeInit 1 */

  /* USER CODE END ADC1_MspDeInit 1 */
  }

}

/**
* @brief TIM_Base MSP Initialization
* This function configures the hardware resources used in this example
* @param htim_base: TIM_Base handle pointer
* @retval None
*/
void HAL_TIM_Base_MspInit(TIM_HandleTypeDef* htim_base)
{
  if(htim_base->Instance==TIM14)
  {
  /* USER CODE BEGIN TIM14_MspInit 0 */

  /* USER CODE END TIM14_MspInit 0 */
    /* Peripheral clock enable */
    __HAL_RCC_TIM14_CLK_ENABLE();
    /* TIM14 interrupt Init */
    HAL_NVIC_SetPriority(TIM14_IRQn, 0, 0);
    HAL_NVIC_EnableIRQ(TIM14_IRQn);
  /* USER CODE BEGIN TIM14_MspInit 1 */

  /* USER CODE END TIM14_MspInit 1 */
  }

}

/**
* @brief TIM_Base MSP De-Initialization
* This function freeze the hardware resources used in this example
* @param htim_base: TIM_Base handle pointer
* @retval None
*/
void HAL_TIM_Base_MspDeInit(TIM_HandleTypeDef* htim_base)
{
  if(htim_base->Instance==TIM14)
  {
  /* USER CODE BEGIN TIM14_MspDeInit 0 */

  /* USER CODE END TIM14_MspDeInit 0 */
    /* Peripheral clock disable */
    __HAL_RCC_TIM14_CLK_DISABLE();

    /* TIM14 interrupt DeInit */
    HAL_NVIC_DisableIRQ(TIM14_IRQn);
  /* USER CODE BEGIN TIM14_MspDeInit 1 */

  /* USER CODE END TIM14_MspDeInit 1 */
  }

}

/**
* @brief UART MSP Initialization
* This function configures the hardware resources used in this example
* @param huart: UART handle pointer
* @retval None
*/
void HAL_UART_MspInit(UART_HandleTypeDef* huart)
{
  GPIO_InitTypeDef GPIO_InitStruct = {0};
  if(huart->Instance==USART1)
  {
  /* USER CODE BEGIN USART1_MspInit 0 */
		
  /* USER CODE END USART1_MspInit 0 */
    /* Peripheral clock enable */
    __HAL_RCC_USART1_CLK_ENABLE();

    __HAL_RCC_GPIOA_CLK_ENABLE();
    /**USART1 GPIO Configuration
    PA9     ------> USART1_TX
    PA10     ------> USART1_RX
    */
    GPIO_InitStruct.Pin = GPIO_PIN_9|GPIO_PIN_10;
    GPIO_InitStruct.Mode = GPIO_MODE_AF_PP;
    GPIO_InitStruct.Pull = GPIO_PULLUP;
    GPIO_InitStruct.Speed = GPIO_SPEED_FREQ_LOW;
    GPIO_InitStruct.Alternate = GPIO_AF1_USART1;
    HAL_GPIO_Init(GPIOA, &GPIO_InitStruct);

    /* USART1 DMA Init */
    /* USART1_TX Init */
    hdma_usart1_tx.Instance = DMA1_Channel1;
    hdma_usart1_tx.Init.Request = DMA_REQUEST_USART1_TX;
    hdma_usart1_tx.Init.Direction = DMA_MEMORY_TO_PERIPH;
    hdma_usart1_tx.Init.PeriphInc = DMA_PINC_DISABLE;
    hdma_usart1_tx.Init.MemInc = DMA_MINC_ENABLE;
    hdma_usart1_tx.Init.PeriphDataAlignment = DMA_PDATAALIGN_BYTE;
    hdma_usart1_tx.Init.MemDataAlignment = DMA_MDATAALIGN_BYTE;
    hdma_usart1_tx.Init.Mode = DMA_NORMAL;
    hdma_usart1_tx.Init.Priority = DMA_PRIORITY_LOW;
    if (HAL_DMA_Init(&hdma_usart1_tx) != HAL_OK)
    {
      Error_Handler();
    }

    __HAL_LINKDMA(huart,hdmatx,hdma_usart1_tx);

    /* USART1 interrupt Init */
    HAL_NVIC_SetPriority(USART1_IRQn, 1, 0);
    HAL_NVIC_EnableIRQ(USART1_IRQn);
  /* USER CODE BEGIN USART1_MspInit 1 */

  /* USER CODE END USART1_MspInit 1 */
  }

}

/**
* @brief UART MSP De-Initialization
* This function freeze the hardware resources used in this example
* @param huart: UART handle pointer
* @retval None
*/
void HAL_UART_MspDeInit(UART_HandleTypeDef* huart)
{
  if(huart->Instance==USART1)
  {
  /* USER CODE BEGIN USART1_MspDeInit 0 */

  /* USER CODE END USART1_MspDeInit 0 */
    /* Peripheral clock disable */
    __HAL_RCC_USART1_CLK_DISABLE();

    /**USART1 GPIO Configuration
    PA9     ------> USART1_TX
    PA10     ------> USART1_RX
    */
    HAL_GPIO_DeInit(GPIOA, GPIO_PIN_9|GPIO_PIN_10);

    /* USART1 DMA DeInit */
    HAL_DMA_DeInit(huart->hdmatx);

    /* USART1 interrupt DeInit */
    HAL_NVIC_DisableIRQ(USART1_IRQn);
  /* USER CODE BEGIN USART1_MspDeInit 1 */

  /* USER CODE END USART1_MspDeInit 1 */
  }

}

/* USER CODE BEGIN 1 */

/* USER CODE END 1 */

/************************ (C) COPYRIGHT STMicroelectronics *****END OF FILE****/

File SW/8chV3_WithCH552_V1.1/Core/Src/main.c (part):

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
 
void ReadSet(void){
  SET_1 = HAL_GPIO_ReadPin(SET1_GPIO_Port,SET1_Pin) == 0; //Debug EN
  SET_2 = HAL_GPIO_ReadPin(SET2_GPIO_Port,SET2_Pin) == 0; //output limit
  SET_3 = HAL_GPIO_ReadPin(SET3_GPIO_Port,SET3_Pin) == 0; //output banlace
  SET_4 = HAL_GPIO_ReadPin(SET4_GPIO_Port,SET4_Pin) == 0; //12ASIA
}


//¼ì²âÅäÖÃ¿ª¹Ø±ä»¯ºó£¬¾ÍÖØÆôic
void checkSet(void){
	if(SET_1 != (HAL_GPIO_ReadPin(SET1_GPIO_Port,SET1_Pin) == 0)){
		HAL_NVIC_SystemReset();
	}
	if(SET_2 != (HAL_GPIO_ReadPin(SET2_GPIO_Port,SET2_Pin) == 0)){
		HAL_NVIC_SystemReset();
	}
	if(SET_3 != (HAL_GPIO_ReadPin(SET3_GPIO_Port,SET3_Pin) == 0)){
		HAL_NVIC_SystemReset();
	}
	if(SET_4 != (HAL_GPIO_ReadPin(SET4_GPIO_Port,SET4_Pin) == 0)){
		HAL_NVIC_SystemReset();
	}
}
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  GPIO_InitStruct.Speed = GPIO_SPEED_FREQ_LOW;
  HAL_GPIO_Init(GPIOB, &GPIO_InitStruct);

  /*Configure GPIO pins : SET1-4_Pin */
  GPIO_InitStruct.Pin = SET3_Pin|SET4_Pin|SET2_Pin|SET1_Pin;
  GPIO_InitStruct.Mode = GPIO_MODE_INPUT;
  GPIO_InitStruct.Pull = GPIO_PULLUP;
  HAL_GPIO_Init(GPIOD, &GPIO_InitStruct);
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  GPIO_InitStruct.Speed = GPIO_SPEED_FREQ_LOW;
  HAL_GPIO_Init(SENSE_GPIO_Port, &GPIO_InitStruct);

  /*Configure GPIO pins : service_Pin */
  GPIO_InitStruct.Pin = KEY_TEST_Pin|KEY_SERVICE_Pin|KEY_ENTER_Pin|KEY_SEL_UP_Pin|KEY_COIN1_Pin;
  GPIO_InitStruct.Mode = GPIO_MODE_INPUT;
  GPIO_InitStruct.Pull = GPIO_NOPULL;
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  GPIO_InitStruct.Speed = GPIO_SPEED_FREQ_LOW;
  HAL_GPIO_Init(GPIOB, &GPIO_InitStruct);

  /*Configure GPIO pins : SET3_Pin SET4_Pin */
  GPIO_InitStruct.Pin = SET3_Pin|SET4_Pin;
  GPIO_InitStruct.Mode = GPIO_MODE_INPUT;
  GPIO_InitStruct.Pull = GPIO_PULLUP;
  HAL_GPIO_Init(GPIOC, &GPIO_InitStruct);

  /*Configure GPIO pins : SET2_Pin SET1_Pin */
  GPIO_InitStruct.Pin = SET2_Pin|SET1_Pin;
  GPIO_InitStruct.Mode = GPIO_MODE_INPUT;
  GPIO_InitStruct.Pull = GPIO_PULLUP;
  HAL_GPIO_Init(GPIOB, &GPIO_InitStruct);
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
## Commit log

2023-10-30 new
    new
2023-10-30 update ign
2023-11-07 add software
2025-06-01 update img
